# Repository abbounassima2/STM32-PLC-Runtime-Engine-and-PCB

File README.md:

# STM32 PLC Runtime Engine and Hardware Design

An STM32F407-based PLC runtime engine developed in Embedded C, together with a custom PLC controller PCB and a Renode-based simulation environment.

The project focuses on designing a **reusable PLC runtime platform** rather than a single-purpose STM32 application. The architecture separates the permanent runtime, hardware abstraction, process image, communication, and user control logic.

---

## Project Goal

The main objective is to develop an embedded PLC platform capable of providing the core functions of a programmable industrial controller:

- PLC operating modes
- Cyclic and periodic program execution
- Process-image based I/O
- Digital and analog I/O management
- Retentive PLC variables
- Industrial communication
- Runtime monitoring
- Real-time task management
- Custom PLC hardware
- Firmware simulation and testing

The long-term architecture is based on separating the **permanent PLC runtime** from the **user program**, providing the foundation for a configurable and programmable embedded PLC.

## Runtime Execution and Validation

The following logs demonstrate PLC operating-mode transitions,
power recovery handling, and runtime execution.

## I/O Mapping Architecture

The following diagrams illustrate the input reading and output
writing processes, including hardware-to-process-image mapping.

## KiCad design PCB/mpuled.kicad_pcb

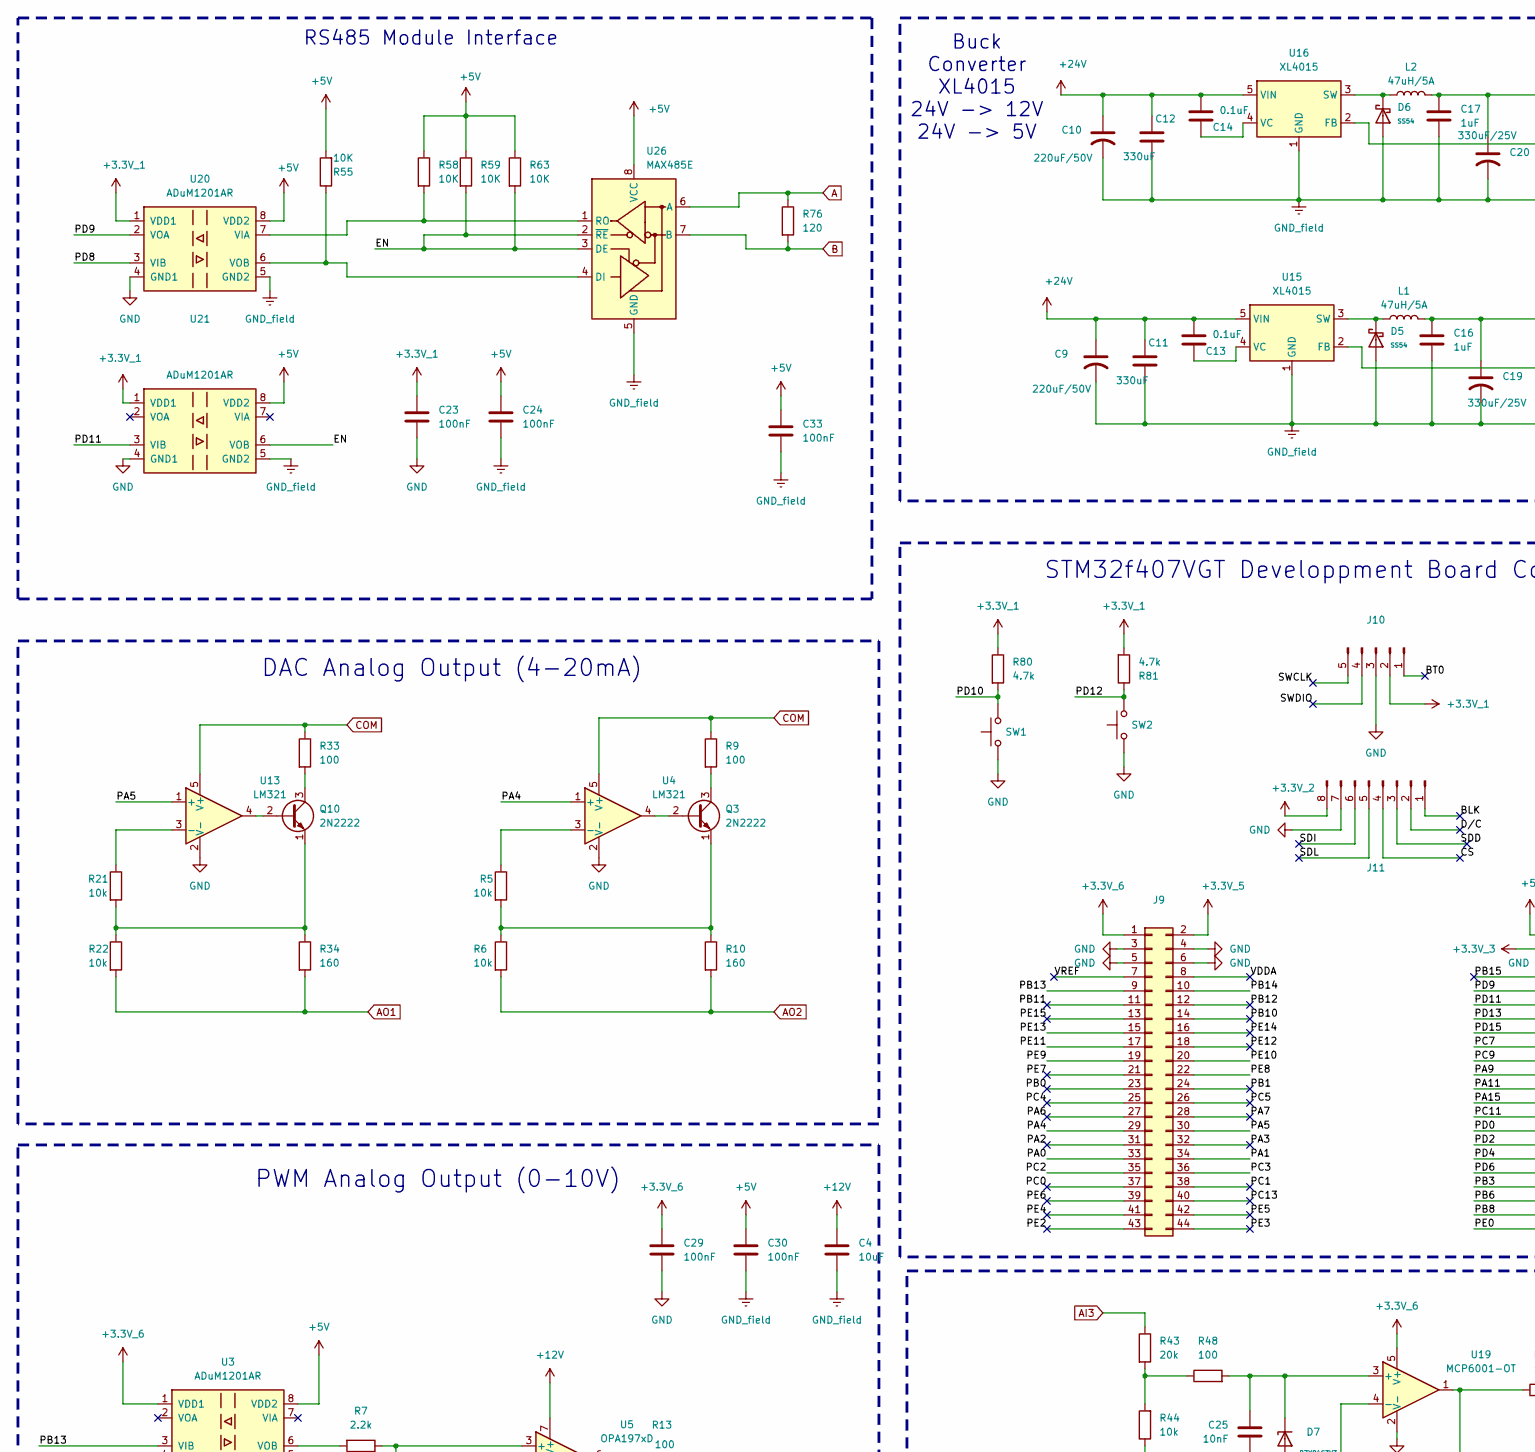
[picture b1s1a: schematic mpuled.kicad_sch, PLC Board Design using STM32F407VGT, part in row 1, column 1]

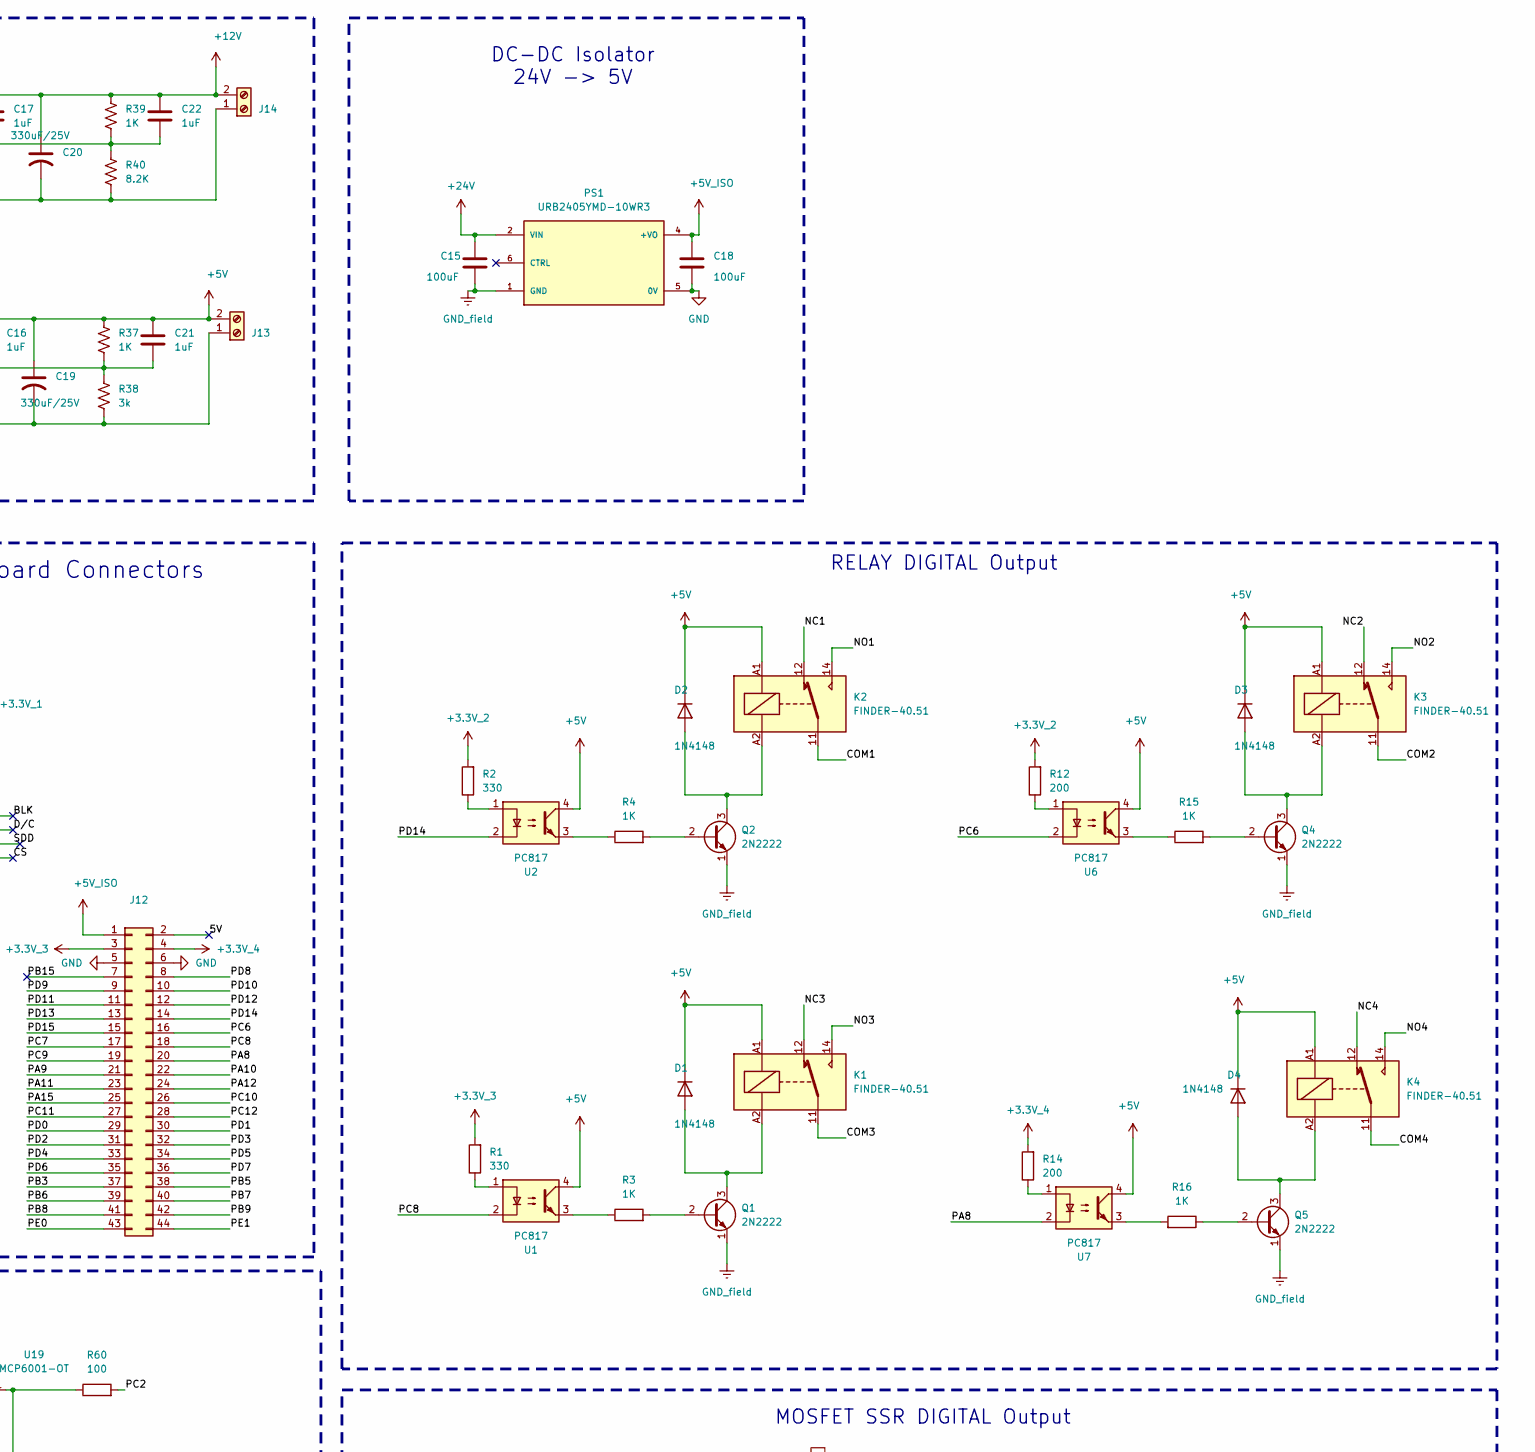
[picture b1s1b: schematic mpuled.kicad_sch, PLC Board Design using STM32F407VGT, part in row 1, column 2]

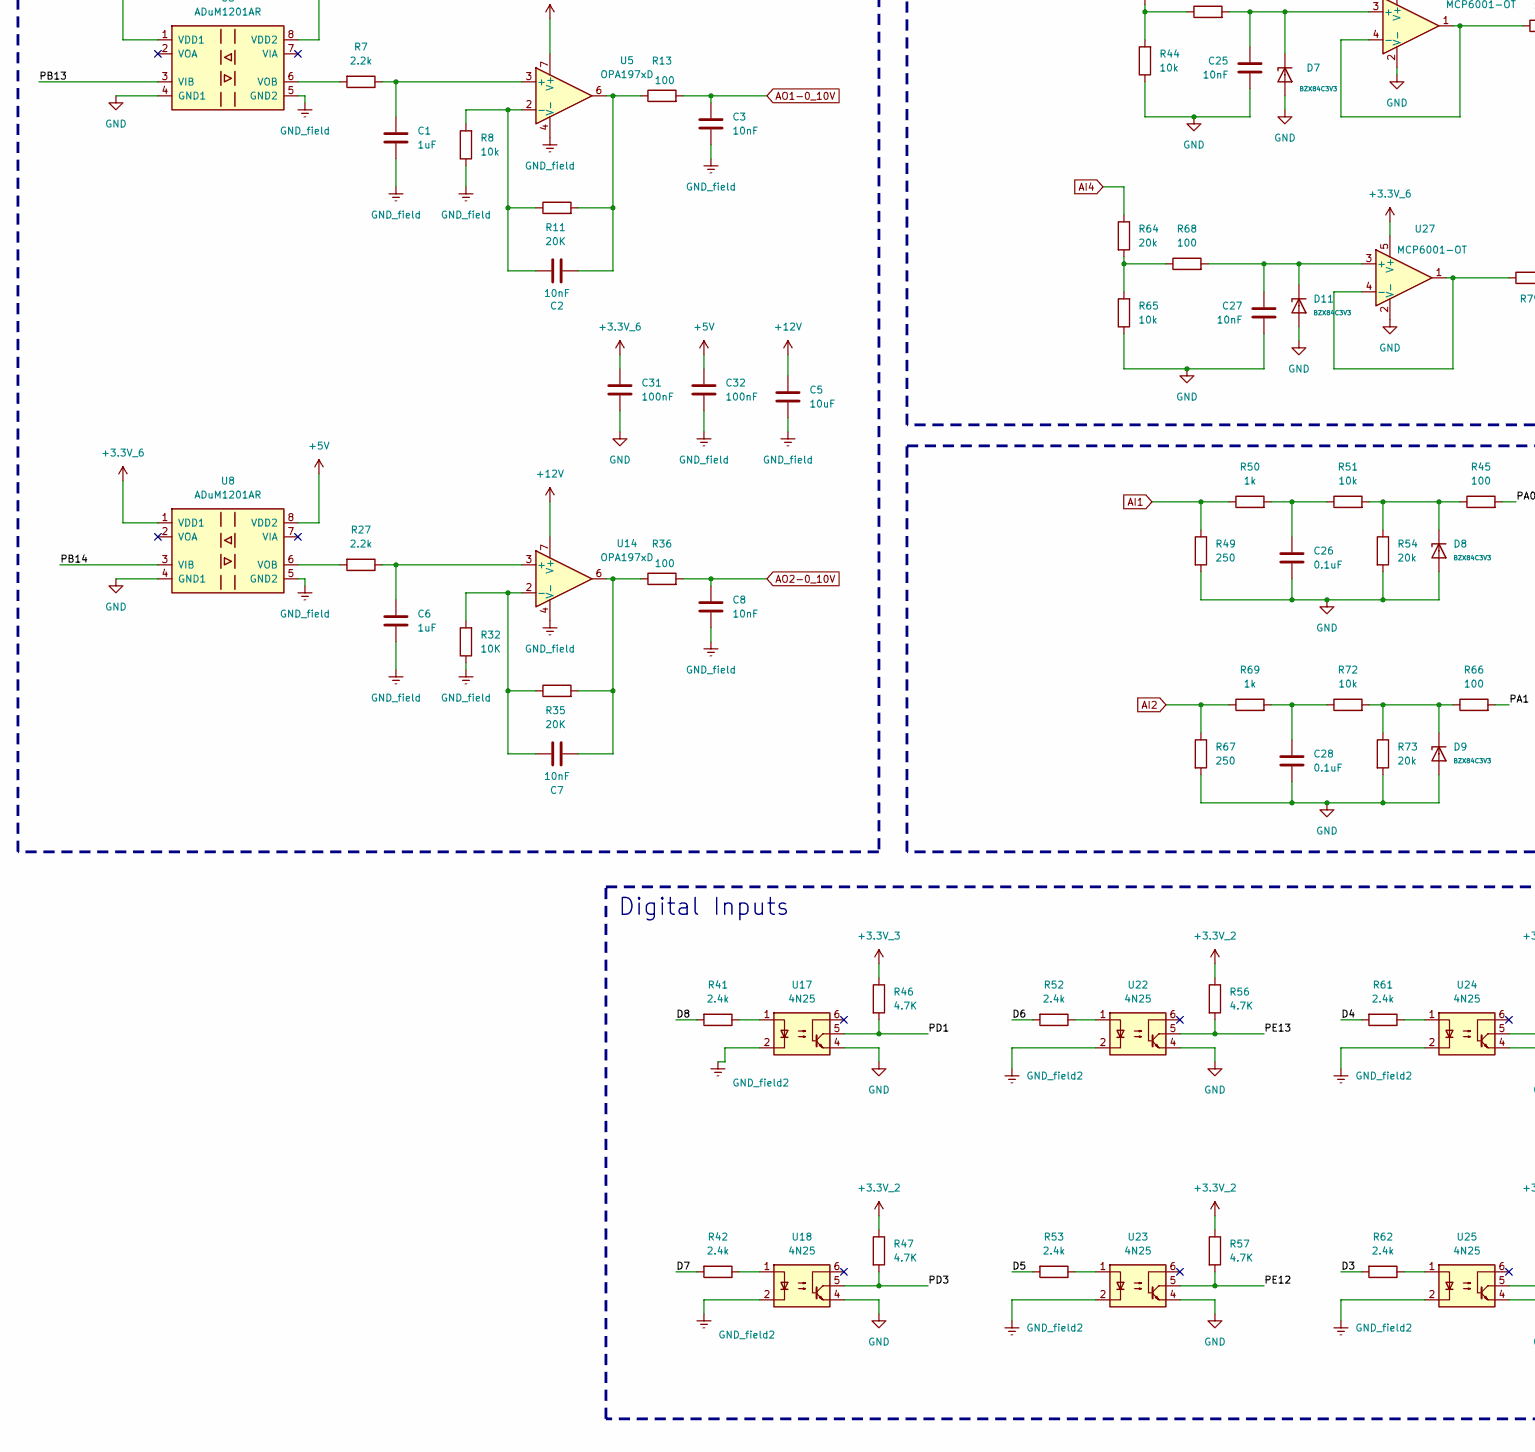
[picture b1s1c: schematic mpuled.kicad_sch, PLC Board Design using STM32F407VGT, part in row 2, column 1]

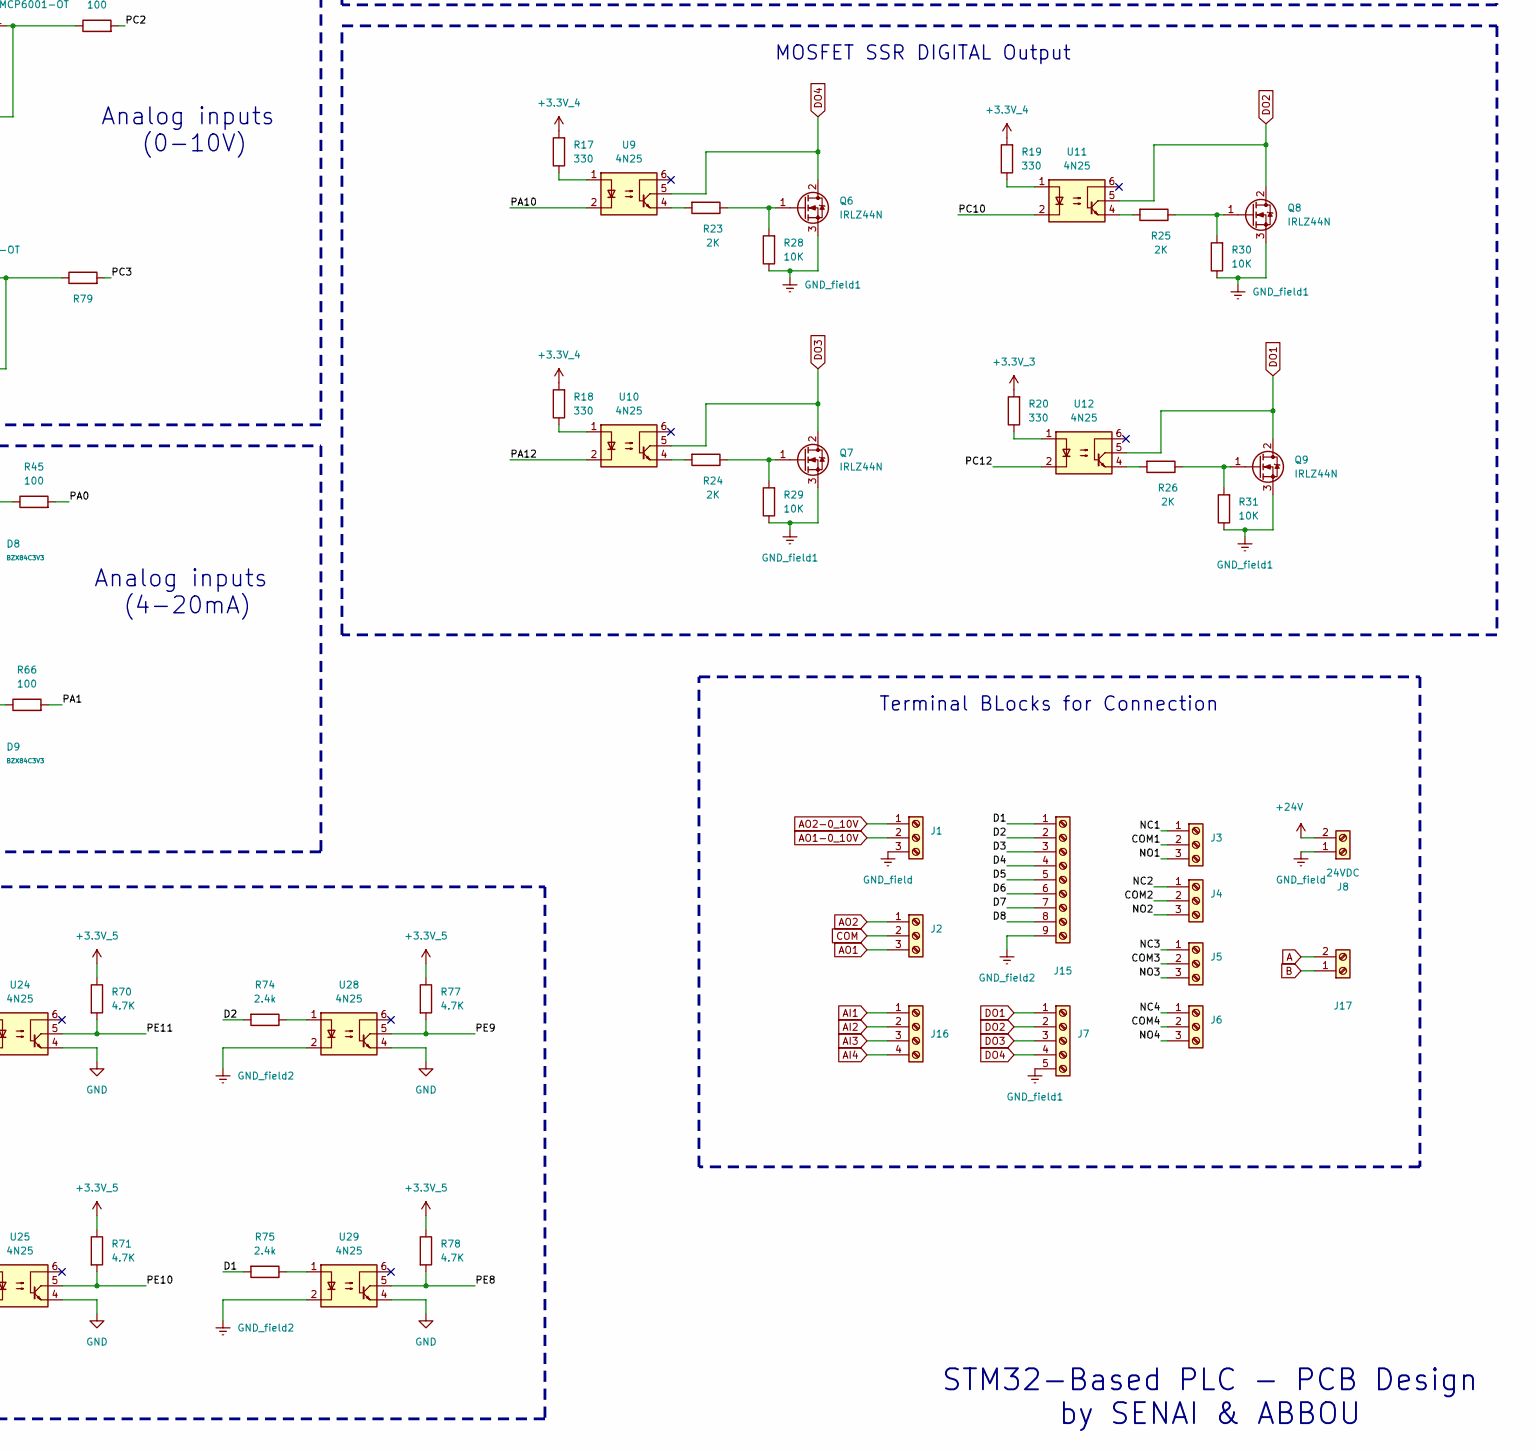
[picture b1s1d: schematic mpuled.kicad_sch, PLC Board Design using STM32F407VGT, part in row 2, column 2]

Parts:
C1, C6, C16, C17, C21, C22: 1uF; C_1206_3216Metric_Pad1.33x1.80mm_HandSolder
C2, C3, C7, C8, C25, C27: 10nF; C_1206_3216Metric_Pad1.33x1.80mm_HandSolder
C4, C5: 10uF; C_1206_3216Metric_Pad1.33x1.80mm_HandSolder
C9, C10: 220uF/50V; C_Radial_D10.0mm_H12.5mm_P5.00mm
C11, C12: 330uF; C_1206_3216Metric_Pad1.33x1.80mm_HandSolder
C13, C14, C26, C28: 0.1uF; C_1206_3216Metric_Pad1.33x1.80mm_HandSolder
C15, C18: 100uF; C_1206_3216Metric_Pad1.33x1.80mm_HandSolder
C19, C20: 330uF/25V; C_Radial_D10.0mm_H12.5mm_P5.00mm
C23, C24, C29, C30, C31, C32, C33: 100nF; C_1206_3216Metric_Pad1.33x1.80mm_HandSolder
D1, D2, D3, D4: 1N4148; D_DO-35_SOD27_P7.62mm_Horizontal
D5, D6: SS54; D_SMA; Forward Voltage (Vf@If) 550mV@5A; Reverse Voltage (Vr) 40V; Part SS54; LCSC C22452
D7, D8, D9, D11: BZX84C3V3; D_SOT-23; Zener Voltage (Range) 3.1V~3.5V; Zener Voltage (Nom) 3.3V; Part BZX84C3V3; LCSC C19077467
J1, J2: Screw_Terminal_01x03; TerminalBlock_Phoenix_MKDS-1,5-3_1x03_P5.00mm_Horizontal
J3, J4, J5, J6: TerminalBlock_Phoenix_MKDS-1,5-3-5.08_1x03_P5.08mm_Horizont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
J7: Screw_Terminal_01x05; TerminalBlock_Phoenix_MKDS-1,5-5-5.08_1x05_P5.08mm_Horizont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
J8: 24VDC; TerminalBlock_Phoenix_MKDS-1,5-2-5.08_1x02_P5.08mm_Horizont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
J9, J12: Conn_02x22_Odd_Even; PinHeader_2x22_P2.54mm_Vertical
J10: PinHeader_1x05_P2.54mm_Vertical
J11: PinHeader_1x08_P2.54mm_Vertical
J13, J14: Screw_Terminal_01x02; TerminalBlock_Phoenix_MKDS-1,5-2_1x02_P5.00mm_Horizontal
J15: Screw_Terminal_01x09; TerminalBlock_Phoenix_MKDS-1,5-9-5.08_1x09_P5.08mm_Horizont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
J16: TerminalBlock_Phoenix_MKDS-1,5-4_1x04_P5.00mm_Horizontal
J17: TerminalBlock_Phoenix_MKDS-1,5-2-5.08_1x02_P5.08mm_Horizont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
K1, K2, K3, K4: FINDER-40.51; Relay_SPDT_Finder_40.51
L1, L2: 47uH/5A; L_Axial_L14.5mm_D5.8mm_P20.32mm_Horizontal_Fastron_HBCC
PS1: URB2405YMD-10WR3; Converter_DCDC_XP_POWER-IAxxxxS_THT; PARTREV 2019.11.13-A/9
Q1, Q4, Q5: 2N2222; SOT-23W_Handsoldering
Q2: 2N2222; TSOT-23_HandSoldering
Q3, Q10: 2N2222; Q_SOT-23
Q6, Q7, Q8, Q9: IRLZ44N; TO-220-3_Vertical
R1, R2, R17, R18, R19, R20: 330; R_1206_3216Metric_Pad1.30x1.75mm_HandSolder
R3, R4, R15, R16, R37, R39: 1K; R_1206_3216Metric_Pad1.30x1.75mm_HandSolder
R5, R6, R8, R21, R22, R44, R51, R65, R72: 10k; R_1206_3216Metric_Pad1.30x1.75mm_HandSolder
R7, R27: 2.2k; R_1206_3216Metric_Pad1.30x1.75mm_HandSolder
R9, R13, R33, R36, R45, R60, R66, R79: 100; R_1206_3216Metric_Pad1.30x1.75mm_HandSolder
R10, R34: 160; R_1206_3216Metric_Pad1.30x1.75mm_HandSolder
R11, R35: 20K; R_1206_3216Metric_Pad1.30x1.75mm_HandSolder
R12, R14: 200; R_1206_3216Metric_Pad1.30x1.75mm_HandSolder
R23, R24, R25, R26: 2K; R_1206_3216Metric_Pad1.30x1.75mm_HandSolder
R28, R29, R30, R31, R32, R55, R58, R59, R63: 10K; R_1206_3216Metric_Pad1.30x1.75mm_HandSolder
R38: 3k; R_1206_3216Metric_Pad1.30x1.75mm_HandSolder
R40: 8.2K; R_1206
R41, R42, R52, R53, R61, R62, R74, R75: 2.4k; R_1206_3216Metric_Pad1.30x1.75mm_HandSolder
R43, R54, R73: 20k; R_1206_3216Metric_Pad1.30x1.75mm_HandSolder
R46, R47, R56, R57, R70, R71, R77, R78: 4.7K; R_1206_3216Metric_Pad1.30x1.75mm_HandSolder
R48, R68: 100; R_1206_3216Metric
R49, R67: 250; R_1206_3216Metric_Pad1.30x1.75mm_HandSolder
R50, R69: 1k; R_1206_3216Metric_Pad1.30x1.75mm_HandSolder
R64: 20k; R_1206_3216Metric
R76: 120; R_1206_3216Metric_Pad1.30x1.75mm_HandSolder
R80, R81: 4.7k; R_1206_3216Metric_Pad1.30x1.75mm_HandSolder
SW1, SW2: SW_Omron_B3FS; SW_SPST_Omron_B3FS-100xP
U1, U2, U6, U7: PC817; DIP-4_W7.62mm
U3, U8, U20, U21: ADuM1201AR; SOIC-8_3.9x4.9mm_P1.27mm
U4, U13: LM321; SOT-23-5_HandSoldering
U5, U14: OPA197xD; SOIC-8_3.9x4.9mm_P1.27mm
U9, U10, U11, U12, U17, U18, U22, U23, U24, U25, U28, U29: 4N25; DIP-6_W7.62mm
U15, U16: XL4015; TO-263-5_TabPin3
U19, U27: MCP6001-OT; SOT-23-5
U26: MAX485E; SOIC-8_3.9x4.9mm_P1.27mm

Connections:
+3.3V_1: C23.1, J10.2, R80.1, R81.2, U20.1 (VDD1), U21.1 (VDD1)
+3.3V_2: J11.8, R2.2, R12.2, R47.1, R56.1, R57.1
+3.3V_3: J12.3, R1.2, R20.2, R46.1
+3.3V_4: J12.4, R14.2, R17.2, R18.2, R19.2
+3.3V_5: J9.2, R70.1, R71.1, R77.1, R78.1
+3.3V_6: C29.1, C31.1, J9.1, U3.1 (VDD1), U8.1 (VDD1), U19.5 (V+), U27.5 (V+)
+5V: C16.1, C19.1, C21.1, C24.1, C30.1, C32.1, C33.1, D1.1 (K), D2.1 (K), D3.1 (K), D4.1 (K), J13.2, K1.A1, K2.A1, K3.A1, K4.A1, L1.2, R37.1, R55.2, R58.1, R59.1, R63.1, U1.4, U2.4, U3.8 (VDD2), U6.4, U7.4, U8.8 (VDD2), U20.8 (VDD2), U21.8 (VDD2), U26.8 (VCC)
+5V_ISO: C18.1, J12.1, PS1.4 (+VO)
+12V: C4.1, C5.1, C17.1, C20.1, C22.1, J14.2, L2.2, R39.1, U5.7 (V+), U14.7 (V+)
+24V: C9.1, C10.1, C11.1, C12.1, C13.1, C14.1, C15.1, J8.2, PS1.2 (VIN), U15.5 (VIN), U16.5 (VIN)
/5V: J12.2
/BLK: J11.1
/BT0: J10.1
/COM1: J3.2, K2.11
/COM2: J4.2, K3.11
/COM3: J5.2, K1.11
/COM4: J6.2, K4.11
/CS: J11.4
/D1: J15.1, R75.2
/D2: J15.2, R74.2
/D3: J15.3, R62.2
/D4: J15.4, R61.2
/D5: J15.5, R53.2
/D6: J15.6, R52.2
/D7: J15.7, R42.2
/D8: J15.8, R41.2
/D/C: J11.2
/EN: R59.2, R63.2, U21.6 (VOB), U26.2 (~RE), U26.3 (DE)
/NC1: J3.1, K2.12
/NC2: J4.1, K3.12
/NC3: J5.1, K1.12
/NC4: J6.1, K4.12
/NO1: J3.3, K2.14
/NO2: J4.3, K3.14
/NO3: J5.3, K1.14
/NO4: J6.3, K4.14
/PA0: J9.33, R45.2
/PA1: J9.34, R66.2
/PA2: J9.31
/PA3: J9.32
/PA4: J9.29, U4.1 (+)
/PA5: J9.30, U13.1 (+)
/PA6: J9.27
/PA7: J9.28
/PA8: J12.20, U7.2
/PA9: J12.21
/PA10: J12.22, U9.2
/PA11: J12.23
/PA12: J12.24, U10.2
/PA15: J12.25
/PB0: J9.23
/PB1: J9.24
/PB3: J12.37
/PB5: J12.38
/PB6: J12.39
/PB7: J12.40
/PB8: J12.41
/PB9: J12.42
/PB10: J9.14
/PB11: J9.11
/PB12: J9.12
/PB13: J9.9, U3.3 (VIB)
/PB14: J9.10, U8.3 (VIB)
/PB15: J12.7
/PC0: J9.37
/PC1: J9.38
/PC2: J9.35, R60.2
/PC3: J9.36, R79.2
/PC4: J9.25
/PC5: J9.26
/PC6: J12.16, U6.2
/PC7: J12.17
/PC8: J12.18, U1.2
/PC9: J12.19
/PC10: J12.26, U11.2
/PC11: J12.27
/PC12: J12.28, U12.2
/PC13: J9.40
/PD0: J12.29
/PD1: J12.30, R46.2, U17.5
/PD2: J12.31
/PD3: J12.32, R47.2, U18.5
/PD4: J12.33
/PD5: J12.34
/PD6: J12.35
/PD7: J12.36
/PD8: J12.8, U20.3 (VIB)
/PD9: J12.9, U20.2 (VOA)
/PD10: J12.10, R80.2, SW1.2
/PD11: J12.11, U21.3 (VIB)
/PD12: J12.12, R81.1, SW2.2
/PD13: J12.13
/PD14: J12.14, U2.2
/PD15: J12.15
/PE0: J12.43
/PE1: J12.44
/PE2: J9.43
/PE3: J9.44
/PE4: J9.41
/PE5: J9.42
/PE6: J9.39
/PE7: J9.21
/PE8: J9.22, R78.2, U29.5
/PE9: J9.19, R77.2, U28.5
/PE10: J9.20, R71.2, U25.5
/PE11: J9.17, R70.2, U24.5
/PE12: J9.18, R57.2, U23.5
/PE13: J9.15, R56.2, U22.5
/PE14: J9.16
/PE15: J9.13
/SDD: J11.3
/SDI: J11.6
/SDL: J11.5
/SWCLK: J10.5
/SWDIO: J10.4
/VDDA: J9.8
/VREF: J9.7
A: J17.2, R76.1, U26.6 (A)
AI1: J16.1, R49.1, R50.1
AI2: J16.2, R67.1, R69.1
AI3: J16.3, R43.1
AI4: J16.4, R64.1
AO1: J2.3, R22.2, R34.2
AO1-0_10V: C3.1, J1.2, R13.2
AO2: J2.1, R6.2, R10.2
AO2-0_10V: C8.1, J1.1, R36.2
B: J17.1, R76.2, U26.7 (B)
COM: J2.2, R9.1, R33.1, U4.5 (V+), U13.5 (V+)
DO1: J7.1, Q9.2 (D), U12.5
DO2: J7.2, Q8.2 (D), U11.5
DO3: J7.3, Q7.2 (D), U10.5
DO4: J7.4, Q6.2 (D), U9.5
GND: C18.2, C23.2, C25.2, C26.2, C27.2, C28.2, C29.2, C31.2, D7.1, D8.1, D9.1, D11.1, J9.3, J9.4, J9.5, J9.6, J10.3, J11.7, J12.5, J12.6, PS1.5 (0V), R44.1, R49.2, R54.2, R65.1, R67.2, R73.2, SW1.1, SW2.1, U3.4 (GND1), U4.2 (V-), U8.4 (GND1), U13.2 (V-), U17.4, U18.4, U19.2 (V-), U20.4 (GND1), U21.4 (GND1), U22.4, U23.4, U24.4, U25.4, U27.2 (V-), U28.4, U29.4
GND_field: C1.2, C3.2, C4.2, C5.2, C6.2, C8.2, C9.2, C10.2, C11.2, C12.2, C15.2, C16.2, C17.2, C19.2, C20.2, C24.2, C30.2, C32.2, C33.2, D5.2, D6.2, J1.3, J8.1, J13.1, J14.1, PS1.1 (GND), Q1.1 (E), Q2.1 (E), Q4.1 (E), Q5.1 (E), R8.1, R32.1, R38.2, R40.2, U3.5 (GND2), U5.4 (V-), U8.5 (GND2), U14.4 (V-), U15.1 (GND), U16.1 (GND), U20.5 (GND2), U21.5 (GND2), U26.5 (GND)
GND_field1: J7.5, Q6.3 (S), Q7.3 (S), Q8.3 (S), Q9.3 (S), R28.1, R29.1, R30.1, R31.1
GND_field2: J15.9, U17.2, U18.2, U22.2, U23.2, U24.2, U25.2, U28.2, U29.2
unnamed: C2.2, R11.2, R13.1, U5.6
unnamed: C7.2, R35.2, R36.1, U14.6
unnamed: C26.1, R50.2, R51.1
unnamed: C28.1, R69.2, R72.1
unnamed: D1.2 (A), K1.A2, Q1.3 (C)
unnamed: D2.2 (A), K2.A2, Q2.3 (C)
unnamed: D3.2 (A), K3.A2, Q4.3 (C)
unnamed: D4.2 (A), K4.A2, Q5.3 (C)
unnamed: D8.3, R45.1, R51.2, R54.1
unnamed: D9.3, R66.1, R72.2, R73.1
unnamed: Q1.2 (B), R3.2
unnamed: Q2.2 (B), R4.2
unnamed: Q3.2 (B), U4.4
unnamed: Q3.3 (C), R9.2
unnamed: Q3.1 (E), R5.2, R6.1, R10.1
unnamed: Q4.2 (B), R15.2
unnamed: Q5.2 (B), R16.1
unnamed: Q6.1 (G), R23.1, R28.2
unnamed: Q7.1 (G), R24.1, R29.2
unnamed: Q8.1 (G), R25.1, R30.2
unnamed: Q9.1 (G), R26.1, R31.2
unnamed: Q10.2 (B), U13.4
unnamed: Q10.3 (C), R33.2
unnamed: Q10.1 (E), R21.2, R22.1, R34.1
unnamed: R1.1, U1.1
unnamed: R2.1, U2.1
unnamed: R3.1, U1.3
unnamed: R4.1, U2.3
unnamed: R12.1, U6.1
unnamed: R14.1, U7.1
unnamed: R15.1, U6.3
unnamed: R16.2, U7.3
unnamed: R17.1, U9.1
unnamed: R18.1, U10.1
unnamed: R19.1, U11.1
unnamed: R20.1, U12.1
unnamed: R23.2, U9.4
unnamed: R24.2, U10.4
unnamed: R25.2, U11.4
unnamed: R26.2, U12.4
unnamed: R41.1, U17.1
unnamed: R42.1, U18.1
unnamed: R43.2, R44.2, R48.1
unnamed: R52.1, U22.1
unnamed: R53.1, U23.1
unnamed: R61.1, U24.1
unnamed: R62.1, U25.1
unnamed: R64.2, R65.2, R68.1
unnamed: R74.1, U28.1
unnamed: R75.1, U29.1
unnamed: R7.2, U3.6 (VOB)
unnamed: R5.1, U4.3 (-)
unnamed: C1.1, R7.1, U5.3 (+)
unnamed: C2.1, R8.2, R11.1, U5.2 (-)
unnamed: R27.2, U8.6 (VOB)
unnamed: R21.1, U13.3 (-)
unnamed: C6.1, R27.1, U14.3 (+)
unnamed: C7.1, R32.2, R35.1, U14.2 (-)
unnamed: C21.2, R37.2, R38.1, U15.2 (FB)
unnamed: D5.1, L1.1, U15.3 (SW)
unnamed: C13.2, U15.4 (VC)
unnamed: C22.2, R39.2, R40.1, U16.2 (FB)
unnamed: D6.1, L2.1, U16.3 (SW)
unnamed: C14.2, U16.4 (VC)
unnamed: C25.1, D7.3, R48.2, U19.3 (+)
unnamed: R60.1, U19.1, U19.4 (-)
unnamed: R58.2, U20.7 (VIA), U26.1 (RO)
unnamed: R55.1, U20.6 (VOB), U26.4 (DI)
unnamed: C27.1, D11.3, R68.2, U27.3 (+)
unnamed: R79.1, U27.1, U27.4 (-)

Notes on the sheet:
DC-DC Isolator 24V -> 5V
RELAY DIGITAL Output
Buck Converter XL4015 24V -> 12V 24V -> 5V
DAC Analog Output (4-20mA)
RS485 Module Interface
Analog inputs (4-20mA)
STM32-Based PLC - PCB Design by SENAI & ABBOU
Terminal BLocks for Connection
Digital Inputs
MOSFET SSR DIGITAL Output
Analog inputs (0-10V)
PWM Analog Output (0-10V)
STM32f407VGT Developpment Board Connectors

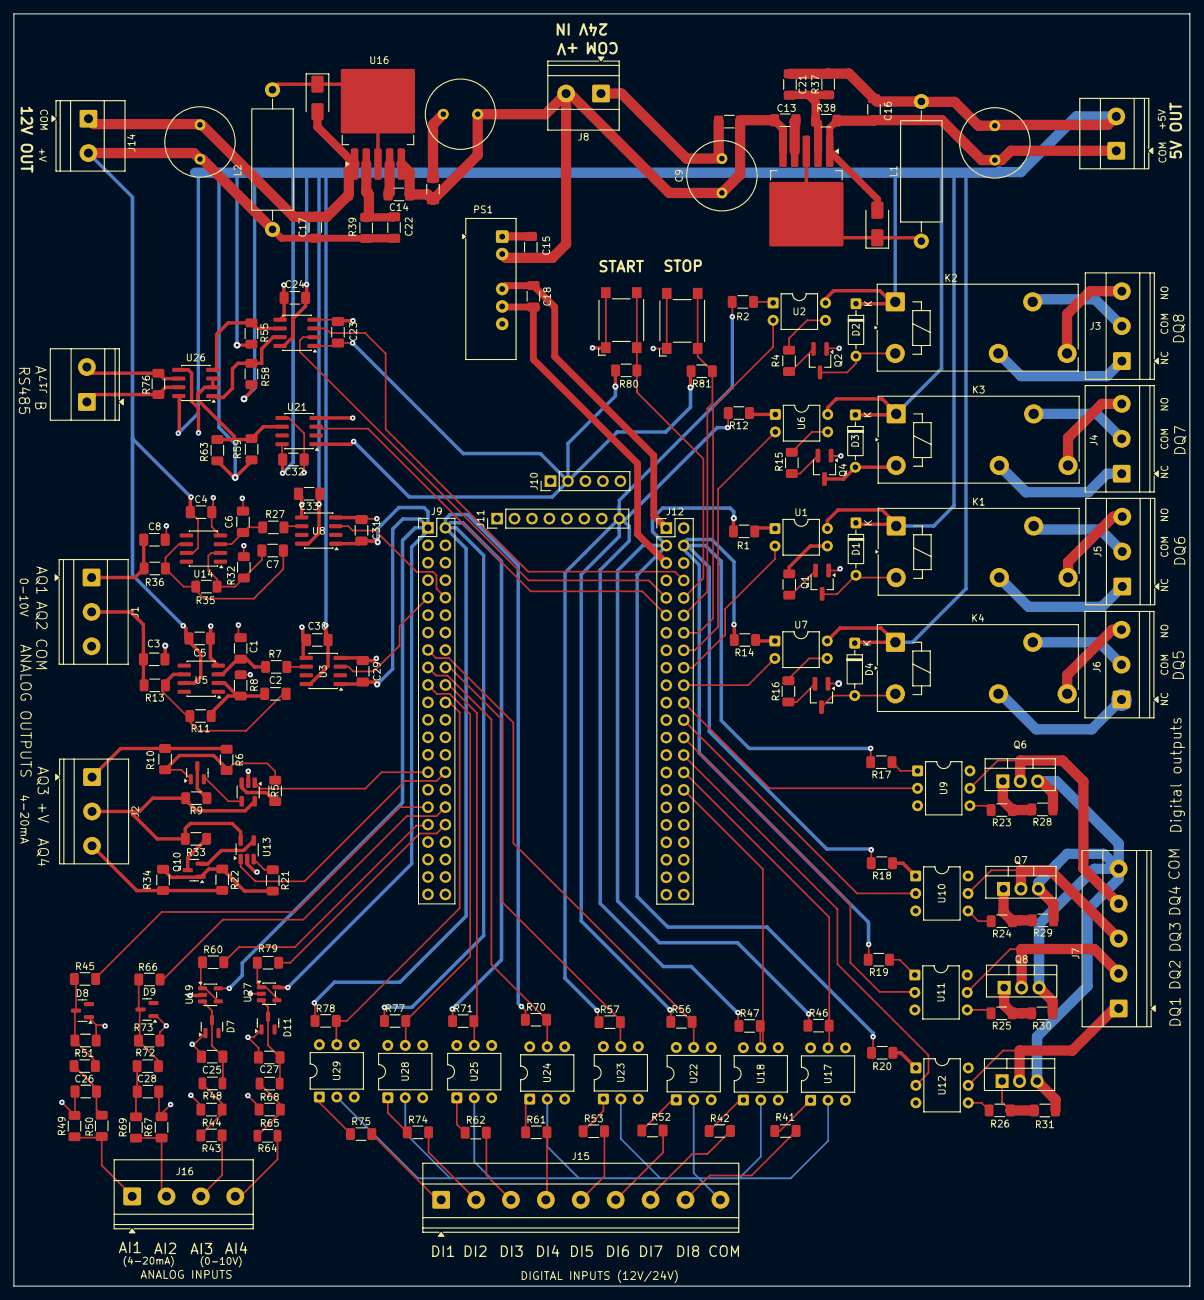
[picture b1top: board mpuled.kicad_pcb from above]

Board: 2 copper layers, 171.1 x 185.1 mm, 189 parts (0 on the bottom side), 149 nets.

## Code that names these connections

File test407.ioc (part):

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Mcu.Name=STM32F407V(E-G)Tx
Mcu.Package=LQFP100
Mcu.UserName=STM32F407VETx
PA0-WKUP.Signal=ADCx_IN0
PA1.Signal=ADCx_IN1
PA10.Signal=GPIO_Output
PA12.Signal=GPIO_Output
PA13.Mode=Serial_Wire
PA13.Signal=SYS_JTMS-SWDIO
PA14.Mode=Serial_Wire
PA14.Signal=SYS_JTCK-SWCLK
PA4.Signal=COMP_DAC1_group
PA5.Signal=COMP_DAC2_group
PA8.Signal=GPIO_Output
PB14.Signal=S_TIM12_CH1
PB15.Signal=S_TIM12_CH2
PC10.Mode=Asynchronous
PC10.Signal=UART4_TX
PC11.Mode=Asynchronous
PC11.Signal=UART4_RX
PC12.Signal=GPIO_Output
PC2.Signal=ADCx_IN12
PC3.Signal=ADCx_IN13
PC6.Signal=GPIO_Output
PC8.Signal=GPIO_Output
PD1.Signal=GPIO_Input
PD11.Signal=GPIO_Output
PD14.Signal=GPIO_Output
PD3.Signal=GPIO_Input
PD8.Mode=Asynchronous
PD8.Signal=USART3_TX
PD9.Mode=Asynchronous
PD9.Signal=USART3_RX
PE10.Signal=GPIO_Input
PE11.Signal=GPIO_Input
PE12.Signal=GPIO_Input
PE13.Signal=GPIO_Input
PE8.Signal=GPIO_Input
PE9.Signal=GPIO_Input
RCC.HSE_VALUE=25000000
RCC.SYSCLKFreq_VALUE=168000000
RCC.SYSCLKSource=RCC_SYSCLKSOURCE_PLLCLK
board=custom
